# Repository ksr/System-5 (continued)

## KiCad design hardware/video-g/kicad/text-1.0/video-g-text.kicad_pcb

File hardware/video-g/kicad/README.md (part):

# VIDEO-G 1.0 - KiCad

The two boards of VIDEO-G (design: [`../DESIGN.md`](../DESIGN.md)). **Generated, not hand-edited:** each board's
circuit is `gen/netlist.py`, its placement `gen/place.py`; `common/build.sh` makes everything else from them. Not
ordered; not built.

| Folder | Board | Size | ICs | Parts list |
|---|---|---|---|---|
| `text-1.0/` | VIDEO-G 1.0 TEXT: 6845 + IDT7134 text, status register, PS/2 keyboard, RCA + DE-9, every decode (all memory-mapped, 7000-7FFF) | **188 x 106.6 mm** (47 mm longer than a standard card: Ken keeps it, 2026-11-17; and since 2026-11-18 10.4 mm more at the +5V end, for the 36-pin bus connector) | 24 | [`text-1.0/BOM.md`](text-1.0/BOM.md) |
| `gfx-1.0/` | VIDEO-G 1.0 GFX: 62256 graphics (two pages), Y and control registers, PS/2 mouse, PWR LED | 141 x 96 mm (standard) | 19 | [`gfx-1.0/BOM.md`](gfx-1.0/BOM.md) |

Both: 4 layers (F.Cu / B.Cu signals, In1.Cu a solid GND plane, In2.Cu a solid +5V plane: MEM3-E's stack-up), the
System-5 bus connector (GFX the 30-pin one; TEXT the 36-pin one since 2026-11-18, for its keyboard flag's choice of four
EF lines: its positions 1-30 where the 30-pin connector's pins were, the board grown at the +5V end) and card-guide
keep-outs where every card has them, the 2 x 20 ribbon header along the same
side edge 78-138 mm from the bus edge (pins 83.6-131.9 mm) (TEXT J6, GFX J4: a straight 40-way cable between neighbouring slots; pin map
`common/ribbon.py`). Silkscreen per Ken's rules: every reference outside its part with the IC type beside it, jacks,
jumpers and the LED labelled by function, the board name and cottageworker.com. **Since 2026-11-18 every text reads
upright with the card standing in the bus, connector down** (Ken's rule for every board; he asked for it on TEXT and
GFX that day): KiCad angle 270, each label at the first spot clear of every pad, part, other text and the card-guide
strips, under its part with the card standing first (`common/silk.py` with `tools/kicad/silk270.py`); the bus pins'
names in two staggered columns (the backplane's names on both boards: `+5V`, `-RESET`); the jumpers' settings at their
ends (TEXT's JP1 NTSC / 5151, JP2 + / -); the name line alone at angle 0 along the bottom edge as drawn, just above the
guide strip (up the right-hand side standing). The copper did not change: `common/silk.py <board>` rewrote the
silkscreen of the routed boards, every track, via, pad and zone checked the same.

**The bus connector is drawn as the part it is since the night of 2026-11-18.** J1 is a single-row right-angle pin
header: its plastic body lies on the board between the pads and the card edge, 1.5 to 4.0 mm from the pads, and its
pins run on past the edge (the photos of the built MEM3-E and BUSDRV-B show it). The C30 and C36 footprints had pads
and a courtyard round them and nothing else, so the label placer and `pcb-check` both took that strip for free board:
`J1 BUS` was printed there on both boards, part of it under the header, and half of TEXT's JP1 label with it. Both
footprints now carry the body (F.Fab), a courtyard round body and pads, and KiCad's 3D model of the header, so the
renders show the connector and the placer keeps every label off it. `J1 BUS` stands past the header's +5V end on GFX
and beside the pin names, between IC1 and IC2, on TEXT; TEXT's `JP1 MONITOR` is under its jumper in the corner past
the header's GND end, `NTSC` and `5151` at the jumper's ends. Silkscreen only, again: `common/silk.py <board>` brings
J1's drawing up to its library file (`tools/kicad/fp_update.py`) and places the labels afresh, and it and
`common/make_board.py` now stop with an error when a label finds no room (the label had been left out without a word).

## Files (per board)

| File | What |
|---|---|
| `gen/netlist.py` | THE circuit: parts, nets, no-connects, what to buy; `python3 gen/netlist.py` checks every symbol pin |
| `gen/place.py` | the placement, silkscreen labels and texts |
| `<board>.kicad_sch` | the working schematic (one sheet, net labels): ERC, the board's parity |
| `<board>.kicad_pcb` | the routed board |
| `schematic/` | the readable schematic, redrawn and proven by `tools/kicad/sch/gen_schematic.py` (in the book `docs/manual/pdf/system5-schematics.pdf`) |
| `reports/` | ERC, DRC, the exported netlist |
| `<board>-gerbers.zip`, `gerbers/`, `check-*.png` | the order files and one picture per copper layer from them |
| `BOM.md` | the parts list (`common/bom.py`) |
| `pcb-check.ini` | `pcb-check`'s settings: name, rev, size, slot pitch, the bus edge, the bus pin list (`tools/s5bus.py`, the bus Rev D's pin names), the system's tests |

`common/`: `symlib.py` (symbol pins from the KiCad libraries), `ribbon.py`, `make_schematic.py`, `checknet.py` (the
exported netlist = `netlist.py`), `make_board.py`, `route.py` (Freerouting in and out, the inner layers as planes),
`route_leftovers.py` (the few connections Freerouting leaves; copied from MEM3-E's), `silk.py` (every label, also on
a routed board: `<KiCad python> common/silk.py <board>` changes the silkscreen only), `bom.py`, `build.sh`.
`lib/video-g-local`: IDT7134, Mini-DIN, RCA and DE-9 from YACC1's Video V2.0 (copied), System-5's C30 bus connector
(GFX), the 36-pin C36 (TEXT; the other 36-pin cards' footprint) and 0.1" bypass-cap footprints (the C30 labels'
stroke raised to 0.15 mm for the fab; 2026-11-17: a courtyard on both and an F.Fab body, 4.0 x 2.5 mm, on the cap, so
that `pcb-check` knows where they are and finds each cap's "100n"; 2026-11-18: the right-angle header's body, a
courtyard round it and its 3D model on C30 and C36, above; 2026-11-19: the RCA jack's body on F.Fab, the outline its
silkscreen has, for `pcb-check`'s new BODIES line, which names a part with nothing drawn on the fab layer: TEXT's J2
was the one. `J2 RCA COMPOSITE` moved 0.15 mm with it, the label placer going by the body where it had gone by the
courtyard). The DE-9, Eagle's F09HP, had only its nine pins' tails on the fab layer, 11 x 3.6 mm of a 31 x 14 mm
connector, which `pcb-check` took for the whole part (its BODIES line names such a drawing since its `0e99e19`): the
connector's outer line is on F.Fab now, and `J3 DE-9 TTL 5151` keeps its place by a spot of its own in `place.py`, the
1.5 mm between the DE-9's back and R4's lead being narrower than the placer's steps. `common/silk.py <board>` brings
the drawing of every part from this library up to its file before it places the labels.

## Rebuild

```sh
hardware/video-g/kicad/common/build.sh hardware/video-g/kicad/gfx-1.0
hardware/video-g/kicad/common/build.sh hardware/video-g/kicad/text-1.0
```

KiCad 10 and Freerouting 1.9 (`~/freerouting/freerouting.jar`). It runs: the netlist check, the schematic and ERC,
the netlist proof, the unrouted board, Freerouting (`MP` passes at most, default 100), the leftover router, DRC with the zones
refilled and schematic parity, the order files, and `tools/preorder_check.py --layers 4`.

**The routing is reproducible since 2026-11-17.** `route.py` writes Freerouting's input in a fixed order and without
the parts' drawn outlines: KiCad lists components, images and pins in a different order on every build (new UUIDs),
and Freerouting's result follows that order and even the outlines (adding two courtyards turned a complete route into
one that stalled), so one build of TEXT left VMA open where the build before had routed everything. Now the same
`gen/` files give the same board. `ROUTE_SEED` in `gen/place.py` shuffles the order reproducibly when one leaves a
net open: TEXT used 7 to 2026-11-24 (seeds 0-10 tried in 2026-11-17's form: nine routed every net, 7 soonest), 0 since. GFX uses 0, the sorted order: rebuilt
the evening of 2026-11-17 with its power LED, it routed every net at once (1697 track segments, 97 vias). The ordering
code is `tools/kicad/dsn_order.py` since then, shared with CPU Rev D (`route.py` gives the same input as before).

**TEXT was routed again on 2026-11-18**, for the 36-pin connector and the 2 x 4 KBD FLAG block: seed 7 still routes
every net (2616 track segments, 133 vias; 3 minutes of routing, then 72 minutes of Freerouting's optimization, so a
full build of TEXT takes about an hour and a quarter). The silkscreen work after it did not need another: a new build
gives Freerouting the same input, byte for byte but for the file's own path, and the same silkscreen to the micrometre
(checked in a copy of the tree).

**TEXT was routed again on 2026-11-24**, with its 6845 write-only (`DESIGN.md`, section 4: seven pins moved, no part and no
silkscreen text changed): seed 0, 2483 track segments and 152 vias. Freerouting routed every net in 4 minutes and then
shortened the tracks for 70; the leftover router had nothing to do; DRC 0 errors and 0 warnings. (Seed 7 routed every net too, but
the track the leftover router made beside J1's pins broke the 0.20 mm clearance in six places.) The 83 parts stand where they
stood, and of the 133 silkscreen texts one moved: `C22 100n`, 0.5 mm, at its size (`place.SPOTS`, `SIZES`; Ken: "move the C22
label clear of IC22"). A 14-pin chip is 19.3 mm long, 0.65 mm past each end of the socket the placer goes by, and the label's
end had been 0.15 mm under it; it is 0.35 mm clear now. Silkscreen only: copper, masks, outline and drills as routed.

After a build: `python3 common/bom.py <board>` and, for the book, `python3 tools/kicad/sch/gen_schematic.py <board>/schematic` and
`python3 tools/kicad/sch/make_book.py`.

## Before ordering

**The latest result, of both boards as they are now (TEXT routed again with its 6845 write-only, 2026-11-24): QA's
run of 2026-11-25 at elf `38fc4d0`, `pcb-check --tests`: TEXT no failures, 0 warnings (netlist 160 of 160; the copper
rebuilt from the gerbers by two methods, which agree; 16 of 16 faults planted in copies of the zip noticed); GFX no
failures, 0 warnings (124 of 124; 16 of 16). The same NOTE on TEXT's EFOC as below. `tools/qa.py full` at `38fc4d0`:
OK.** The results below are of TEXT before that route.

**`pcb-check`, the check before an order (Ken, every system, since 2026-11-06; `hardware/BUILD-RULES.md`, section 2):
both boards as they were before TEXT's route of 2026-11-24, with `--tests`, 2026-11-19: GFX at elf `77257f1` (run by the pcb-check session); TEXT at
`77257f1` (the same), at `688e6ed` after its four KBD FLAG names moved 0.5 mm off JP3's outline, at `b4692e9`
(pcb-check `bd032dd`, with its new BODIES line) after the RCA jack's body went on the fab layer, and at `b2252b7`
(pcb-check `0b45f65`) after the DE-9's; GFX again at `b2252b7` without its tests, the board unchanged:**

```sh
~/Developer/pcb-check/pcb-check hardware/video-g/kicad/text-1.0/video-g-text.kicad_pcb hardware/video-g/kicad/text-1.0/video-g-text-gerbers.zip --layers 4 --tests
~/Developer/pcb-check/pcb-check hardware/video-g/kicad/gfx-1.0/video-g-gfx.kicad_pcb hardware/video-g/kicad/gfx-1.0/video-g-gfx-gerbers.zip --layers 4 --tests
```

| Board | Result | For Ken's eye |
|---|---|---|
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
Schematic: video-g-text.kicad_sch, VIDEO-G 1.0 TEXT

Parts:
C1, C2, C3, C4, C5, C6, C7, C8, C9, C10, C11, C12, C13, C14, C15, C16, C17, C18, C19, C20, C21, C22, C23, C24, C25, C27: 100n; C025-050X050
C26: 47u 16V; CP_Radial_D6.3mm_P2.50mm
C28, C29: 22p; C025-050X050
F1: 0.5A PTC; Fuse_Bourns_MF-RHT050
IC1: 74HCT373; DIP-20_W7.62mm_Socket
IC2: 74LS85; DIP-16_W7.62mm_Socket
IC3: IDT7134; DIP-48_W15.24mm_Socket
IC4: HD68B45SP; DIP-40_W15.24mm_Socket
IC5, IC6, IC7: 74HCT138; DIP-16_W7.62mm_Socket
IC8: 74LS244; DIP-20_W7.62mm_Socket
IC9: 74HCT374; DIP-20_W7.62mm_Socket
IC10: ATmega328P-PU; DIP-28_W7.62mm_Socket
IC11: 74LS374; DIP-20_W7.62mm_Socket
IC12: AT28C64B-15; DIP-28_W15.24mm_Socket
IC13: 74LS166; DIP-16_W7.62mm_Socket
IC14: 74LS175; DIP-16_W7.62mm_Socket
IC15: 74F163A; DIP-16_W7.62mm_Socket
IC16, IC17: 74LS04; DIP-14_W7.62mm_Socket
IC18: 74HCT08; DIP-14_W7.62mm_Socket
IC19: 74LS08; DIP-14_W7.62mm_Socket
IC20: 74LS32; DIP-14_W7.62mm_Socket
IC21: 74LS10; DIP-14_W7.62mm_Socket
IC22: 74LS86; DIP-14_W7.62mm_Socket
IC23: 7416; DIP-14_W7.62mm_Socket
IC24: 74HCT74; DIP-14_W7.62mm_Socket
J1: System-5 bus (36); C36
J2: RCA
J3: DE-9 F; F09HP
J4: KEYBOARD; MiniDIN6_MD-60SM
J5: FTDI; PinHeader_1x06_P2.54mm_Vertical
J6: TO GFX; IDC-Header_2x20_P2.54mm_Vertical
JP1: MONITOR; PinHeader_1x03_P2.54mm_Vertical
JP2: VSYNC; PinHeader_1x03_P2.54mm_Vertical
JP3: KBD FLAG; PinHeader_2x04_P2.54mm_Vertical
LED1: PWR; LED_D5.0mm
R1, R2, R3: 1k; R_Axial_DIN0207_L6.3mm_D2.5mm_P2.54mm_Vertical
R4, R11, R12, R13: 33; R_Axial_DIN0207_L6.3mm_D2.5mm_P2.54mm_Vertical
R5: 270; R_Axial_DIN0207_L6.3mm_D2.5mm_P2.54mm_Vertical
R6: 330; R_Axial_DIN0207_L6.3mm_D2.5mm_P2.54mm_Vertical
R7: 10k; R_Axial_DIN0207_L6.3mm_D2.5mm_P2.54mm_Vertical
R8, R9, R10: 4.7k; R_Axial_DIN0207_L6.3mm_D2.5mm_P2.54mm_Vertical
RN1: 10k x4; R_Array_SIP5
RN2, RN3: 10k x5; R_Array_SIP6
SV1: BLOCK; PinHeader_2x04_P2.54mm_Vertical
Y1: 12MHz; Crystal_HC49-U_Vertical
Y2: 16MHz; Crystal_HC49-U_Vertical

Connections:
+5V: C1.1, C2.1, C3.1, C4.1, C5.1, C6.1, C7.1, C8.1, C9.1, C10.1, C11.1, C12.1, C13.1, C14.1, C15.1, C16.1, C17.1, C18.1, C19.1, C20.1, C21.1, C22.1, C23.1, C24.1, C25.1, C26.1, F1.1, IC1.20 (VCC), IC2.16 (VCC), IC3.2 (R/~WL), IC3.48 (VCC), IC4.20 (VCC), IC5.16 (VCC), IC6.16 (VCC), IC7.16 (VCC), IC8.17 (I3b), IC8.20 (VCC), IC9.20 (VCC), IC10.7 (VCC), IC10.20 (AVCC), IC11.20 (VCC), IC12.27 (~WE), IC12.28 (VCC), IC13.16 (VCC), IC14.16 (VCC), IC15.1 (~MR), IC15.6 (D3), IC15.16 (VCC), IC16.14 (VCC), IC17.14 (VCC), IC18.5, IC18.14 (VCC), IC19.14 (VCC), IC20.14 (VCC), IC21.9, IC21.11, IC21.14 (VCC), IC22.14 (VCC), IC23.14 (VCC), IC24.1 (~R), IC24.4 (~S), IC24.10 (~S), IC24.12 (D), IC24.14 (VCC), J1.30, JP1.3, R3.2, R5.1, R6.2, R7.2, R8.2, R9.2, R10.2, RN1.1 (common), RN2.1 (common)
/-BOARDSEL: IC17.6, IC20.12
/-CRTCCS: IC4.25 (~CS), IC5.15 (O0)
/-EF: J1.6, JP3.7, RN2.2 (R1)
/-EF1: J1.31, JP3.1
/-EF2: J1.32, JP3.3
/-EF3: J1.33, JP3.5
/-MRD: IC3.43 (~OER), IC6.5 (E2), J1.18
/-MRW: IC3.46 (R/~WR), IC7.5 (E2), J1.17
/-RDKEY: IC6.14 (O1), IC9.1 (OE), IC20.9
/-RDMOUSE: IC6.12 (O3), J6.31
/-RDSTAT: IC6.13 (O2), IC8.1 (OEa), IC8.19 (OEb)
/-RESET: IC4.2 (~RESET), IC18.4, IC19.5, J1.4, RN2.4 (R3)
/-TXTCE: IC3.47 (~CER), IC20.11
/-VMA: IC16.9, J1.5, RN2.3 (R2)
/-WRCRTC: IC7.15 (O0), IC21.10
/-WRCTL: IC7.13 (O2), J6.26
/-WRY: IC7.12 (O3), J6.30
/A0: IC1.3 (D0), IC3.42 (A0R), IC4.24 (RS), J1.16
/A1: IC1.4 (D1), IC3.41 (A1R), IC5.1 (A0), IC6.1 (A0), IC7.1 (A0), J1.15
/A2: IC1.7 (D2), IC3.40 (A2R), IC5.2 (A1), IC6.2 (A1), IC7.2 (A1), J1.14
/A3: IC1.8 (D3), IC3.39 (A3R), J1.13
/A4: IC1.13 (D4), IC3.38 (A4R), J1.12
/A5: IC1.14 (D5), IC3.37 (A5R), J1.11
/A6: IC1.17 (D6), IC3.36 (A6R), J1.10
/A7: IC1.18 (D7), IC3.35 (A7R), J1.9
/A8: IC1.2 (O0), IC3.34 (A8R)
/A9: IC1.5 (O1), IC3.33 (A9R)
/A10: IC1.6 (O2), IC3.44 (A10R), IC5.4 (E1), IC6.4 (E1), IC7.4 (E1), IC19.13
/A11: IC1.9 (O3), IC18.13, IC20.13
/A12: IC1.12 (O4), IC2.9 (B0)
/A13: IC1.15 (O5), IC2.11 (B1)
/A14: IC1.16 (O6), IC2.14 (B2)
/A15: IC1.19 (O7), IC2.1 (B3)
/ATTR1: IC14.4 (D0), IC22.3
/ATTR2: IC14.2 (Q0), IC14.5 (D1)
/ATTR3: IC14.7 (Q1), IC22.4
/BOARDSEL: IC2.6 (Oa=b), IC17.5, IC18.12
/CA3: IC11.2 (O0), IC12.7 (A3)
/CA4: IC11.5 (O1), IC12.6 (A4)
/CA5: IC11.6 (O2), IC12.5 (A5)
/CA6: IC11.9 (O3), IC12.4 (A6)
/CA7: IC11.12 (O4), IC12.3 (A7)
/CA8: IC11.15 (O5), IC12.25 (A8)
/CA9: IC11.16 (O6), IC12.24 (A9)
/CG0: IC12.11 (I/O0), IC13.2 (A)
/CG1: IC12.12 (I/O1), IC13.3 (B)
/CG2: IC12.13 (I/O2), IC13.4 (C)
/CG3: IC12.15 (I/O3), IC13.5 (D)
/CG4: IC12.16 (I/O4), IC13.10 (E)
/CG5: IC12.17 (I/O5), IC13.11 (F)
/CG6: IC12.18 (I/O6), IC13.12 (G)
/CG7: IC12.19 (I/O7), IC13.14 (H)
/CHARCLOCK: IC11.11 (Cp), IC13.15 (PE), IC14.9 (Cp), IC15.9 (~PE), IC16.12, R12.1
/CNTEN: IC13.9 (Clr), IC14.1 (~Mr), IC15.7 (CEP), IC15.10 (CET), R3.1
/CNTQA: IC15.14 (Q0), IC22.12
/CNTQB: IC15.13 (Q1), IC22.13
/CRTCCLK: IC4.21 (CLK), IC15.12 (Q2), IC20.4, R13.1
/CRTCE: IC4.23 (E), IC21.8
/CURSOR: IC4.19 (CURSOR), IC22.1
/D0: IC3.25 (I/O0R), IC4.33 (D0), IC8.18 (O0a), IC9.2 (O0), J1.29
/D1: IC3.26 (I/O1R), IC4.32 (D1), IC8.16 (O1a), IC9.5 (O1), J1.28
/D2: IC3.27 (I/O2R), IC4.31 (D2), IC8.14 (O2a), IC9.6 (O2), J1.27
/D3: IC3.28 (I/O3R), IC4.30 (D3), IC8.12 (O3a), IC9.9 (O3), J1.26
/D4: IC3.29 (I/O4R), IC4.29 (D4), IC8.9 (O0b), IC9.12 (O4), J1.25
/D5: IC3.30 (I/O5R), IC4.28 (D5), IC8.7 (O1b), IC9.15 (O5), J1.24
/D6: IC3.31 (I/O6R), IC4.27 (D6), IC8.5 (O2b), IC9.16 (O6), J1.23
/D7: IC3.32 (I/O7R), IC4.26 (D7), IC8.3 (O3b), IC9.19 (O7), J1.22
/DE: IC4.18 (DE), IC8.8 (I3a), IC14.12 (D2)
/DE2: IC14.10 (Q2), IC14.13 (D3)
/DE3: IC14.15 (Q3), IC21.5
/DE9VS: J3.9, JP2.2
/DOTCLK: IC13.7 (Clk), IC15.2 (CP), IC16.6, R11.1
/EFOC: IC23.8, JP3.2, JP3.4, JP3.6, JP3.8
/FDTR: C27.1, J5.6
/FRX: IC10.3 (PD1), J5.5
/FTX: IC10.2 (PD0), J5.4
/GDOT: IC20.2, IC21.2, J6.33, RN3.3 (R2)
/GFXPRES: IC8.13 (I1b), J6.36, RN3.5 (R4)
/GOR: IC20.3, IC21.3
/HSBUF: IC19.8, IC23.5, J3.8
/HSYNC: IC4.39 (HS), IC19.9, IC19.10
/KCLK: IC10.4 (PD2), J4.5 (CLK), R9.1
/KCLR: IC19.6, IC24.13 (~R)
/KDAT: IC10.6 (PD4), J4.1 (DATA), R10.1
/KRDT: IC19.4, IC20.8
/KREADY: IC8.2 (I0a), IC10.16 (PB2), IC23.9, IC24.9 (Q)
/LDDATA: IC9.11 (Cp), IC10.12 (PD6), IC24.11 (C), RN2.5 (R4)
/MA0: IC3.6 (A0L), IC4.4 (MA0), J6.2
/MA1: IC3.7 (A1L), IC4.5 (MA1), J6.3
/MA2: IC3.8 (A2L), IC4.6 (MA2), J6.4
/MA3: IC3.9 (A3L), IC4.7 (MA3), J6.5
/MA4: IC3.10 (A4L), IC4.8 (MA4), J6.6
/MA5: IC3.11 (A5L), IC4.9 (MA5), J6.7
/MA6: IC3.12 (A6L), IC4.10 (MA6), J6.8
/MA7: IC3.13 (A7L), IC4.11 (MA7), J6.9
/MA8: IC3.14 (A8L), IC4.12 (MA8), J6.10
/MA9: IC3.15 (A9L), IC4.13 (MA9), J6.11
/MA10: IC3.4 (A10L), IC4.14 (MA10), J6.12
/MA11: IC3.3 (A11L), IC4.15 (MA11)
/MD0: IC9.3 (D0), IC10.23 (PC0)
/MD1: IC9.4 (D1), IC10.24 (PC1)
/MD2: IC9.7 (D2), IC10.25 (PC2)
/MD3: IC9.8 (D3), IC10.26 (PC3)
/MD4: IC9.13 (D4), IC10.27 (PC4)
/MD5: IC9.14 (D5), IC10.28 (PC5)
/MD6: IC9.17 (D6), IC10.14 (PB0)
/MD7: IC9.18 (D7), IC10.15 (PB1)
/MONITOR: IC8.11 (I0b), JP1.2, RN3.2 (R1)
/MREADY: IC8.4 (I1a), J6.35, RN3.4 (R3)
/MRST: C27.2, IC10.1 (~RESET/PC6), IC23.12, R7.1
/NBOTH: IC21.4, IC21.12
/NVSYNC: IC17.8, JP2.3
/OSCIN: IC16.1, R1.1, Y1.1
/OSCMID: IC16.2, IC16.3, R1.2, R2.1
/OSCOUT: IC16.4, IC16.5, R2.2, Y1.2
/PS2VCC: F1.2, J4.4 (+5V)
/PWRLED: LED1.2 (A), R6.1
/QCR: IC20.6, J6.23
/RA0: IC4.38 (RA0), IC12.10 (A0), J6.13
/RA1: IC4.37 (RA1), IC12.9 (A1), J6.14
/RA2: IC4.36 (RA2), IC12.8 (A2), J6.15
/RCHARCLK: J6.19, R12.2
/RCO: IC15.15 (TC), IC16.13, IC20.5
/RDOTCLK: J6.17, R11.2
/RESETB: IC18.6, IC23.11
/RESETH: IC23.10, IC23.13, R8.1
/RQC: J6.21, R13.2
/SEL0: IC2.10 (A0), RN1.2 (R1), SV1.7
/SEL1: IC2.12 (A1), RN1.3 (R2), SV1.5
/SEL2: IC2.13 (A2), RN1.4 (R3), SV1.3
/SEL3: IC2.15 (A3), RN1.5 (R4), SV1.1
/SYNC: IC23.4, IC23.6, J2.C1 (C), R4.1, R5.2
/TD: IC19.1, IC22.6
/TDG: IC19.3, IC20.1, IC21.1
/TDOT: IC13.13 (Qh), IC22.5
/TEXTON: IC19.2, J6.27, RN2.6 (R5)
/TPA: IC1.11 (LE), J1.20
/TPB: IC17.3, J1.19
/TPBN: IC17.4, IC20.10
/UPPER: IC5.6 (E3), IC6.6 (E3), IC7.6 (E3), IC18.11, IC19.12
/VD0: IC3.16 (I/O0L), IC11.3 (D0)
/VD1: IC3.17 (I/O1L), IC11.4 (D1)
/VD2: IC3.18 (I/O2L), IC11.7 (D2)
/VD3: IC3.19 (I/O3L), IC11.8 (D3)
/VD4: IC3.20 (I/O4L), IC11.13 (D4)
/VD5: IC3.21 (I/O5L), IC11.14 (D5)
/VD6: IC3.22 (I/O6L), IC11.17 (D6)
/VD7: IC3.23 (I/O7L), IC22.2
/VIDEO: IC23.2, J3.7, R4.2
/VIDN: IC21.6, IC23.1
/VMA: IC2.3 (Ia=b), IC16.8
/VSBUF: IC17.9, IC18.3, IC23.3, JP2.1
/VSYNC: IC4.40 (VS), IC8.6 (I2a), IC18.1, IC18.2
/WEPH: IC22.11, J6.24
/WSEL: IC19.11, J6.29
/XORM: IC21.13, J6.28, RN3.6 (R5)
/XT1: C28.1, IC10.9 (XTAL1/PB6), Y2.1
/XT2: C29.1, IC10.10 (XTAL2/PB7), Y2.2
GND: C1.2, C2.2, C3.2, C4.2, C5.2, C6.2, C7.2, C8.2, C9.2, C10.2, C11.2, C12.2, C13.2, C14.2, C15.2, C16.2, C17.2, C18.2, C19.2, C20.2, C21.2, C22.2, C23.2, C24.2, C25.2, C26.2, C28.2, C29.2, IC1.1 (OE), IC1.10 (GND), IC2.2 (Ia<b), IC2.4 (Ia>b), IC2.8 (GND), IC3.1 (~CEL), IC3.5 (~OEL), IC3.24 (GND), IC3.45 (A11R), IC4.1 (GND), IC4.3 (LPSTB), IC4.22 (R/~W), IC5.3 (A2), IC5.5 (E2), IC5.8 (GND), IC6.3 (A2), IC6.8 (GND), IC7.3 (A2), IC7.8 (GND), IC8.10 (GND), IC8.15 (I2b), IC9.10 (GND), IC10.8 (GND), IC10.22 (GND), IC11.1 (OE), IC11.10 (GND), IC11.18 (D7), IC12.2 (A12), IC12.14 (GND), IC12.20 (~CE), IC12.21 (A10), IC12.22 (~OE), IC12.23 (A11), IC13.1 (Ds), IC13.6 (CE), IC13.8 (GND), IC14.8 (GND), IC15.3 (D0), IC15.4 (D1), IC15.5 (D2), IC15.8 (GND), IC16.7 (GND), IC16.11, IC17.1, IC17.7 (GND), IC17.11, IC17.13, IC18.7 (GND), IC18.9, IC18.10, IC19.7 (GND), IC20.7 (GND), IC21.7 (GND), IC22.7 (GND), IC22.9, IC22.10, IC23.7 (GND), IC24.2 (D), IC24.3 (C), IC24.7 (GND), J1.1, J2.S1 (S), J2.S2 (S), J2.S3 (S), J3.1, J3.2, J3.G1 (SHELL), J3.G2 (SHELL), J4.3 (GND), J4.S (SHELL), J5.1, J5.2, J6.1, J6.16, J6.18, J6.20, J6.22, J6.25, J6.32, J6.34, J6.37, J6.38, J6.39, J6.40, JP1.1, LED1.1 (K), RN3.1 (common), SV1.2, SV1.4, SV1.6, SV1.8

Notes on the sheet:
VIDEO-G 1.0 TEXT (hardware/video-g/DESIGN.md): the System-5 text card of VIDEO-G; works alone, or with the GFX board on the J6 ribbon.
Memory-mapped, no I/O ports (2026-11-17). Block jumper SV1: 1-2 only = block 7. 7000-77FF text RAM (IDT7134); 7C00-7FFF the GFX window (WSEL).
Registers (7800-7BFF, pairs repeating): 7800/7801 the 6845 (RS = A0); 7802 key (+ a bus flag line while KEY-READY: JP3 picks -EF1, -EF2, -EF3 or -EF); 7804 status / control (GFX); 7806 mouse / Y (GFX).
Status: 0 KEY-READY 1 MOUSE-READY 2 VSYNC 3 DE 4 MONITOR 5 GFX-PRESENT, 7-6 = 10. Reads while -MRD is low; writes while -MRW is low.
6845: write-only (2026-11-24): R/-W on ground, E = the whole -MRW time of a write to 7800/7801 (IC7, IC21C); a read of 7800/7801 finds nothing.

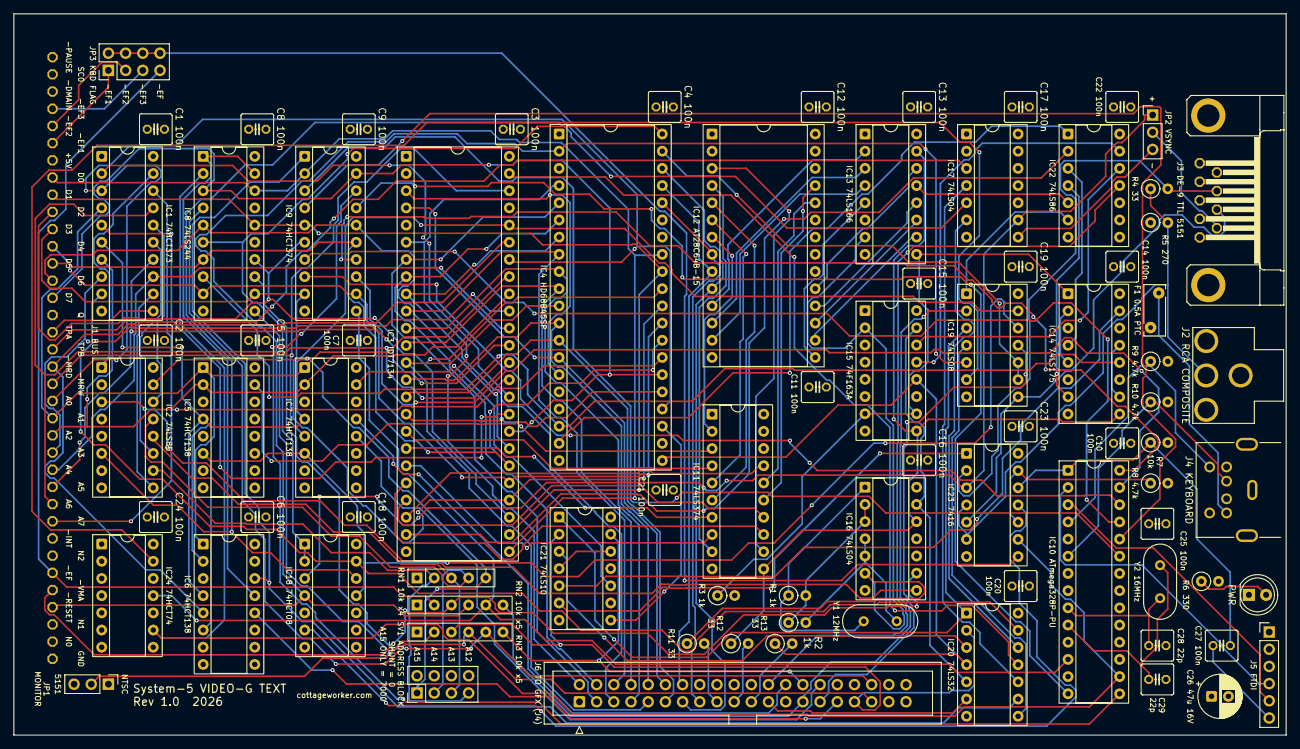
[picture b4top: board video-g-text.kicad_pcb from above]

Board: 4 copper layers, 188.0 x 106.6 mm, 83 parts (0 on the bottom side), 160 nets.

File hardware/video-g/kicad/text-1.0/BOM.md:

# VIDEO-G 1.0 TEXT - bill of materials

Written by `hardware/video-g/kicad/common/bom.py` from `gen/netlist.py` (2026-11-24). Every IC goes in a socket.

| Qty | Value | Footprint | References | What to buy |
|---|---|---|---|---|
| 1 | 74HCT373 | DIP-20_W7.62mm_Socket | IC1 | 74HCT373 (CMOS inputs: no load on the 1802's address lines) |
| 1 | 74LS85 | DIP-16_W7.62mm_Socket | IC2 |  |
| 1 | IDT7134 | DIP-48_W15.24mm_Socket | IC3 | IDT7134SA or LA, 55-90 ns, DIP-48 (600 mil); the 6845 card's chip also fits |
| 1 | HD68B45SP | DIP-40_W15.24mm_Socket | IC4 | HD68B45SP (Hitachi) or MC68B45P (Motorola), the 2 MHz grade; since the 6845 is write-only (E = the whole -MRW) the bus timing of a 1 MHz part, such as the 6845 card's HD6845, is enough as well (DESIGN.md section 4) |
| 3 | 74HCT138 | DIP-16_W7.62mm_Socket | IC5, IC6, IC7 | 74HCT138 (CMOS inputs on the bus address) |
| 1 | 74LS244 | DIP-20_W7.62mm_Socket | IC8 |  |
| 1 | 74HCT374 | DIP-20_W7.62mm_Socket | IC9 |  |
| 1 | ATmega328P-PU | DIP-28_W7.62mm_Socket | IC10 | ATmega328P-PU with the Arduino Uno bootloader burned (ISP) before fitting |
| 1 | 74LS374 | DIP-20_W7.62mm_Socket | IC11 |  |
| 1 | AT28C64B-15 | DIP-28_W15.24mm_Socket | IC12 | AT28C64B-15PU (Microchip), burned on the T48 with firmware/video-g-chargen/video-g-chargen.bin |
| 1 | 74LS166 | DIP-16_W7.62mm_Socket | IC13 |  |
| 1 | 74LS175 | DIP-16_W7.62mm_Socket | IC14 |  |
| 1 | 74F163A | DIP-16_W7.62mm_Socket | IC15 | 74F163A or 74ALS163B (V2.0 review R3-1: CHARCLOCK set-up to the 166's SH/-LD); keep a spare |
| 2 | 74LS04 | DIP-14_W7.62mm_Socket | IC16, IC17 |  |
| 1 | 74HCT08 | DIP-14_W7.62mm_Socket | IC18 |  |
| 1 | 74LS08 | DIP-14_W7.62mm_Socket | IC19 |  |
| 1 | 74LS32 | DIP-14_W7.62mm_Socket | IC20 |  |
| 1 | 74LS10 | DIP-14_W7.62mm_Socket | IC21 |  |
| 1 | 74LS86 | DIP-14_W7.62mm_Socket | IC22 |  |
| 1 | 7416 | DIP-14_W7.62mm_Socket | IC23 |  |
| 1 | 74HCT74 | DIP-14_W7.62mm_Socket | IC24 |  |
| 1 | 12MHz | Crystal_HC49-U_Vertical | Y1 | 12 MHz, HC-49/U |
| 1 | 16MHz | Crystal_HC49-U_Vertical | Y2 | 16 MHz, HC-49/U, 18-20 pF load |
| 1 | System-5 bus (36) | C36 | J1 | 1 x 36 right-angle pin header, 2.54 mm, single row (cut from a 1 x 40): its plastic body lies between the pads and the card edge, the pins out past the edge |
| 1 | RCA | RCA | J2 | RCA jack, right-angle PCB mount (YACC1 V1.0 card's footprint) |
| 1 | DE-9 F | F09HP | J3 | DE-9 female, right-angle PCB mount (F09HP footprint: 2.74 mm pitch, 2.54 mm between rows) |
| 1 | KEYBOARD | MiniDIN6_MD-60SM | J4 | Same Sky (CUI Devices) MD-60SM, date code after 2022-03-03 |
| 1 | FTDI | PinHeader_1x06_P2.54mm_Vertical | J5 | 1 x 6 pin header, 2.54 mm (an FTDI cable programs the ATmega) |
| 1 | TO GFX | IDC-Header_2x20_P2.54mm_Vertical | J6 | 2 x 20 shrouded box header, 2.54 mm; 40-way IDC ribbon (two 2 x 20 IDC sockets, about 10 cm) |
| 1 | BLOCK | PinHeader_2x04_P2.54mm_Vertical | SV1 | 2 x 4 pin header + 1 shunt on 1-2 (block 7, 7000); each fitted shunt is a 0 bit |
| 1 | MONITOR | PinHeader_1x03_P2.54mm_Vertical | JP1 | 1 x 3 pin header + shunt: 1-2 NTSC, 2-3 IBM 5151 |
| 1 | VSYNC | PinHeader_1x03_P2.54mm_Vertical | JP2 | 1 x 3 pin header + shunt: 1-2 +VSYNC, 2-3 -VSYNC (5151) |
| 1 | KBD FLAG | PinHeader_2x04_P2.54mm_Vertical | JP3 | 2 x 4 pin header + 1 shunt: the keyboard flag on -EF1, -EF2, -EF3 or -EF (set to -EF, the fourth pair) |
| 1 | 0.5A PTC | Fuse_Bourns_MF-RHT050 | F1 | Bourns MF-RHT050 (0.5 A hold, radial) |
| 1 | PWR | LED_D5.0mm | LED1 |  |
| 1 | 10k x4 | R_Array_SIP5 | RN1 | 10k x4 BUSSED, pin 1 common, 5-pin SIP (e.g. Bourns 4605X-101-103LF) |
| 2 | 10k x5 | R_Array_SIP6 | RN2, RN3 | 10k x5 BUSSED, pin 1 common, 6-pin SIP (e.g. Bourns 4606X-101-103LF) |
| 3 | 1k | R_Axial_DIN0207_L6.3mm_D2.5mm_P2.54mm_Vertical | R1, R2, R3 | 1/4 W metal film, mounted standing |
| 4 | 33 | R_Axial_DIN0207_L6.3mm_D2.5mm_P2.54mm_Vertical | R4, R11, R12, R13 | 1/4 W metal film, mounted standing |
| 1 | 270 | R_Axial_DIN0207_L6.3mm_D2.5mm_P2.54mm_Vertical | R5 | 1/4 W metal film, mounted standing |
| 1 | 330 | R_Axial_DIN0207_L6.3mm_D2.5mm_P2.54mm_Vertical | R6 | 1/4 W metal film, mounted standing |
| 1 | 10k | R_Axial_DIN0207_L6.3mm_D2.5mm_P2.54mm_Vertical | R7 | 1/4 W metal film, mounted standing |
| 3 | 4.7k | R_Axial_DIN0207_L6.3mm_D2.5mm_P2.54mm_Vertical | R8, R9, R10 | 1/4 W metal film, mounted standing |
| 26 | 100n | C025-050X050 | C1, C2, C3, C4, C5, C6, C7, C8, C9, C10, C11, C12, C13, C14, C15, C16, C17, C18, C19, C20, C21, C22, C23, C24, C25, C27 | ceramic X7R, 50 V, 0.1 in (2.54 mm) lead spacing |
| 1 | 47u 16V | CP_Radial_D6.3mm_P2.50mm | C26 | 47 uF electrolytic, 16 V or more, radial 6.3 mm, 2.5 mm pitch |
| 2 | 22p | C025-050X050 | C28, C29 | ceramic C0G (NP0), 50 V, 0.1 in lead spacing |

**IC sockets:** 9 x DIP-14, 300 mil, 7 x DIP-16, 300 mil, 4 x DIP-20, 300 mil, 1 x DIP-28, 300 mil, 1 x DIP-28, 600 mil, 1 x DIP-40, 600 mil, 1 x DIP-48, 600 mil

**Jumper shunts:** 4 x 2.54 mm, one each for JP1, JP2, JP3, SV1.

Totals: 24 ICs, 83 parts.

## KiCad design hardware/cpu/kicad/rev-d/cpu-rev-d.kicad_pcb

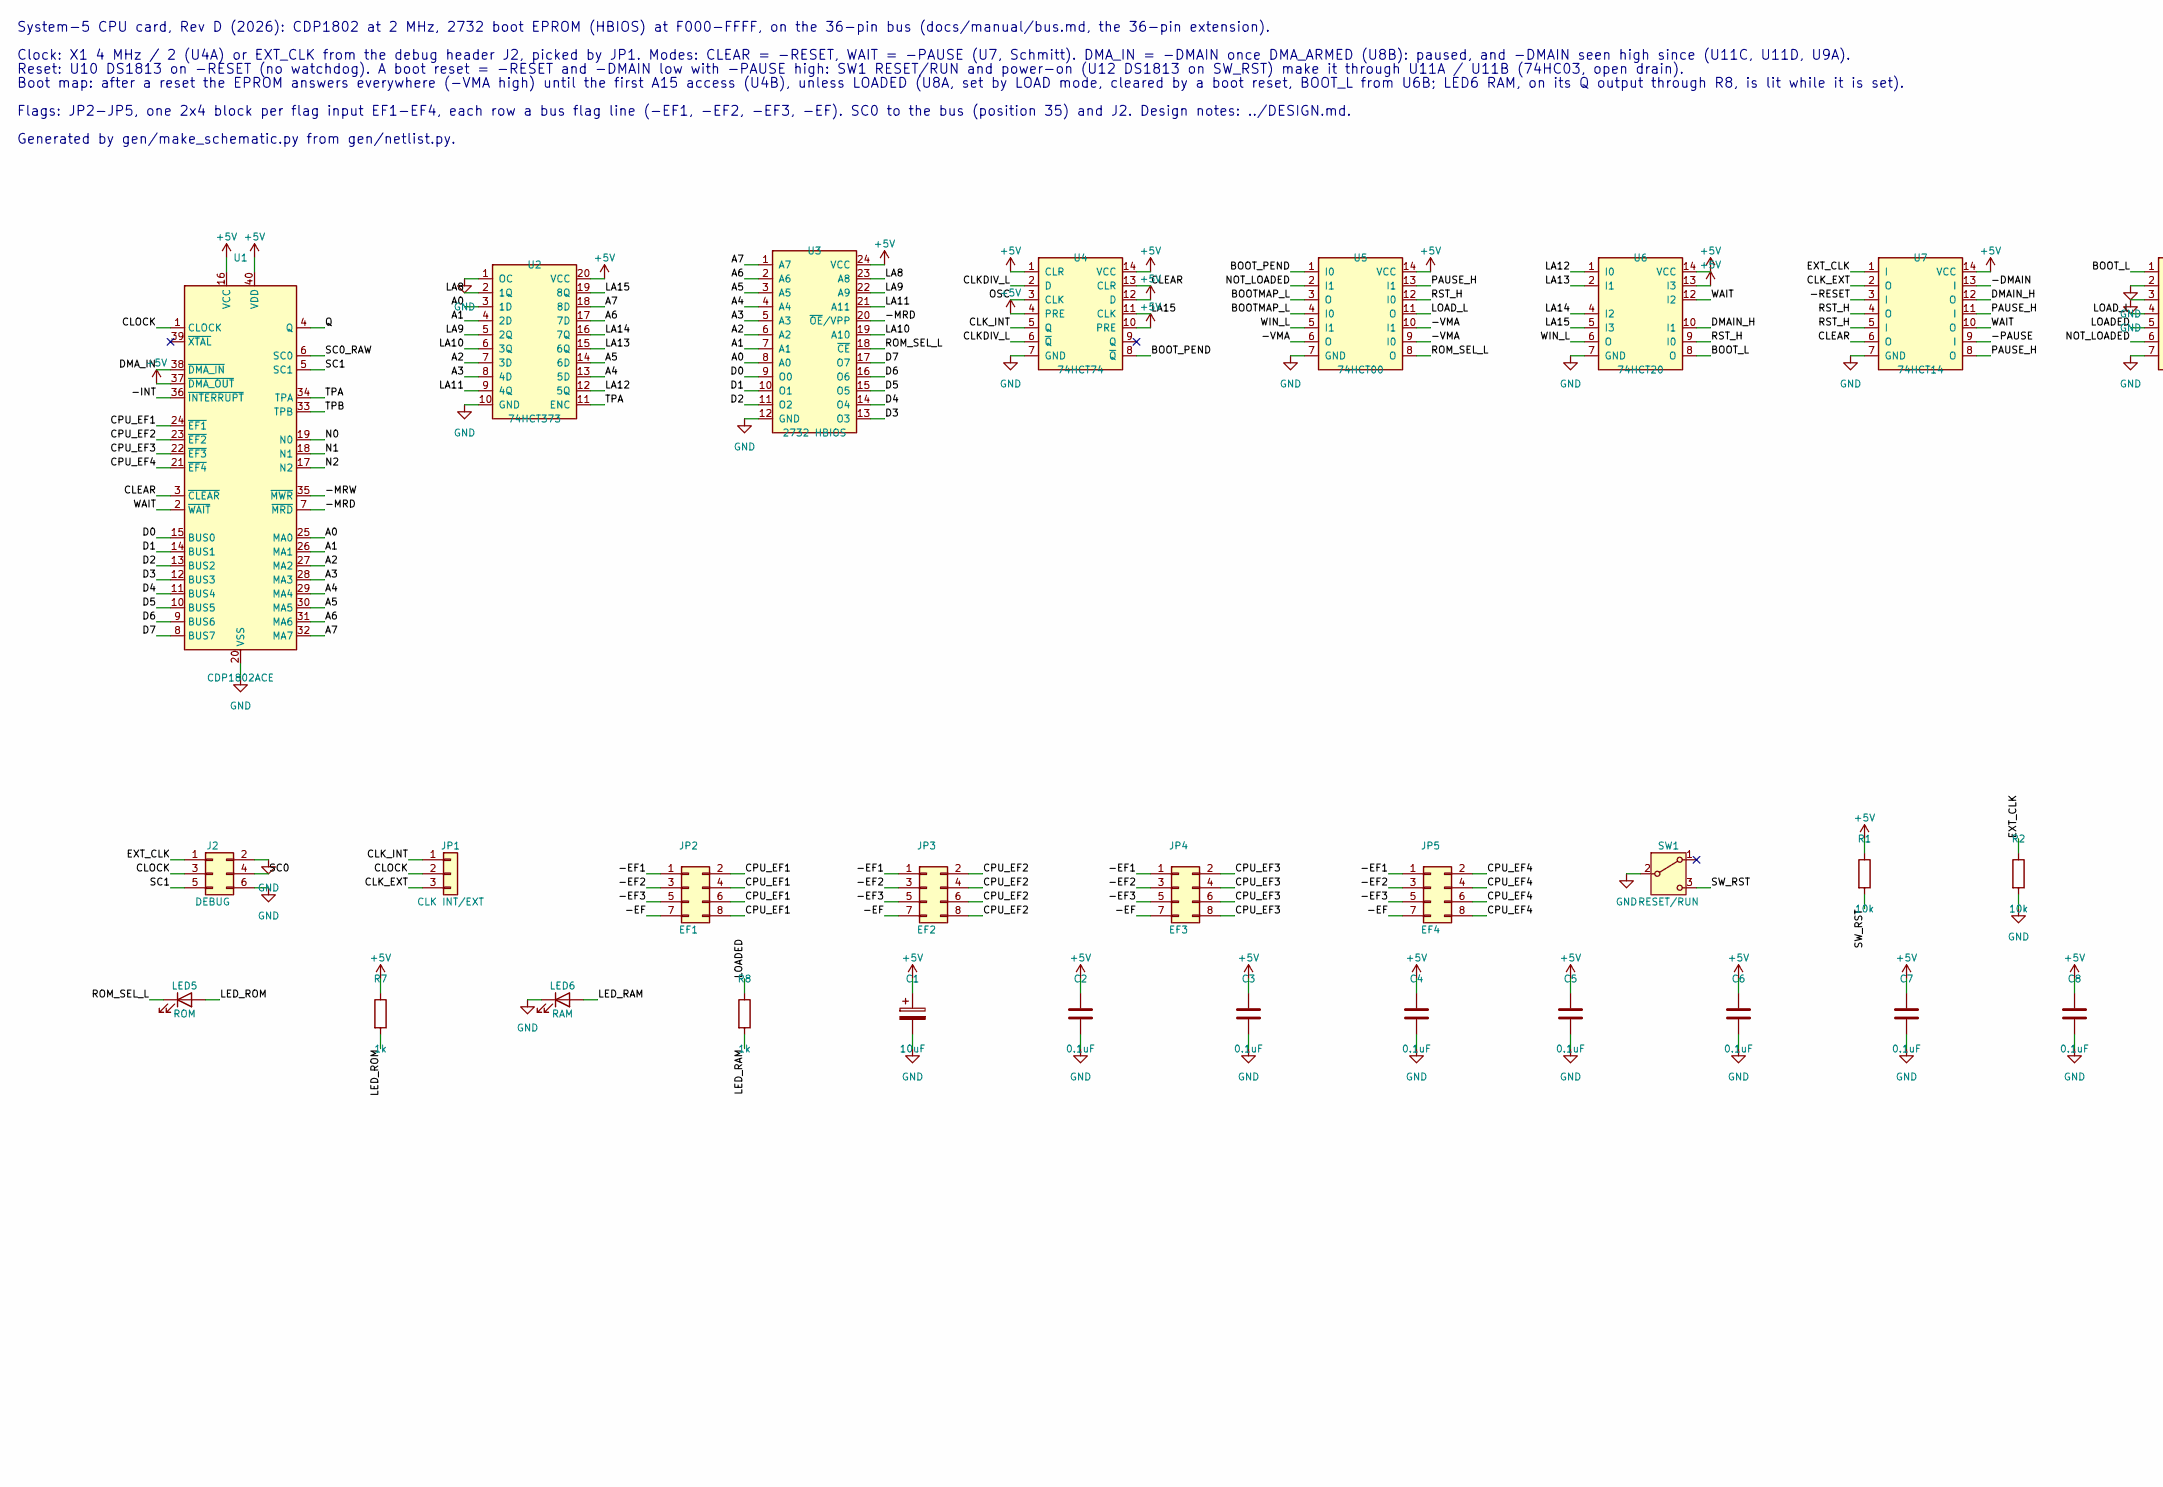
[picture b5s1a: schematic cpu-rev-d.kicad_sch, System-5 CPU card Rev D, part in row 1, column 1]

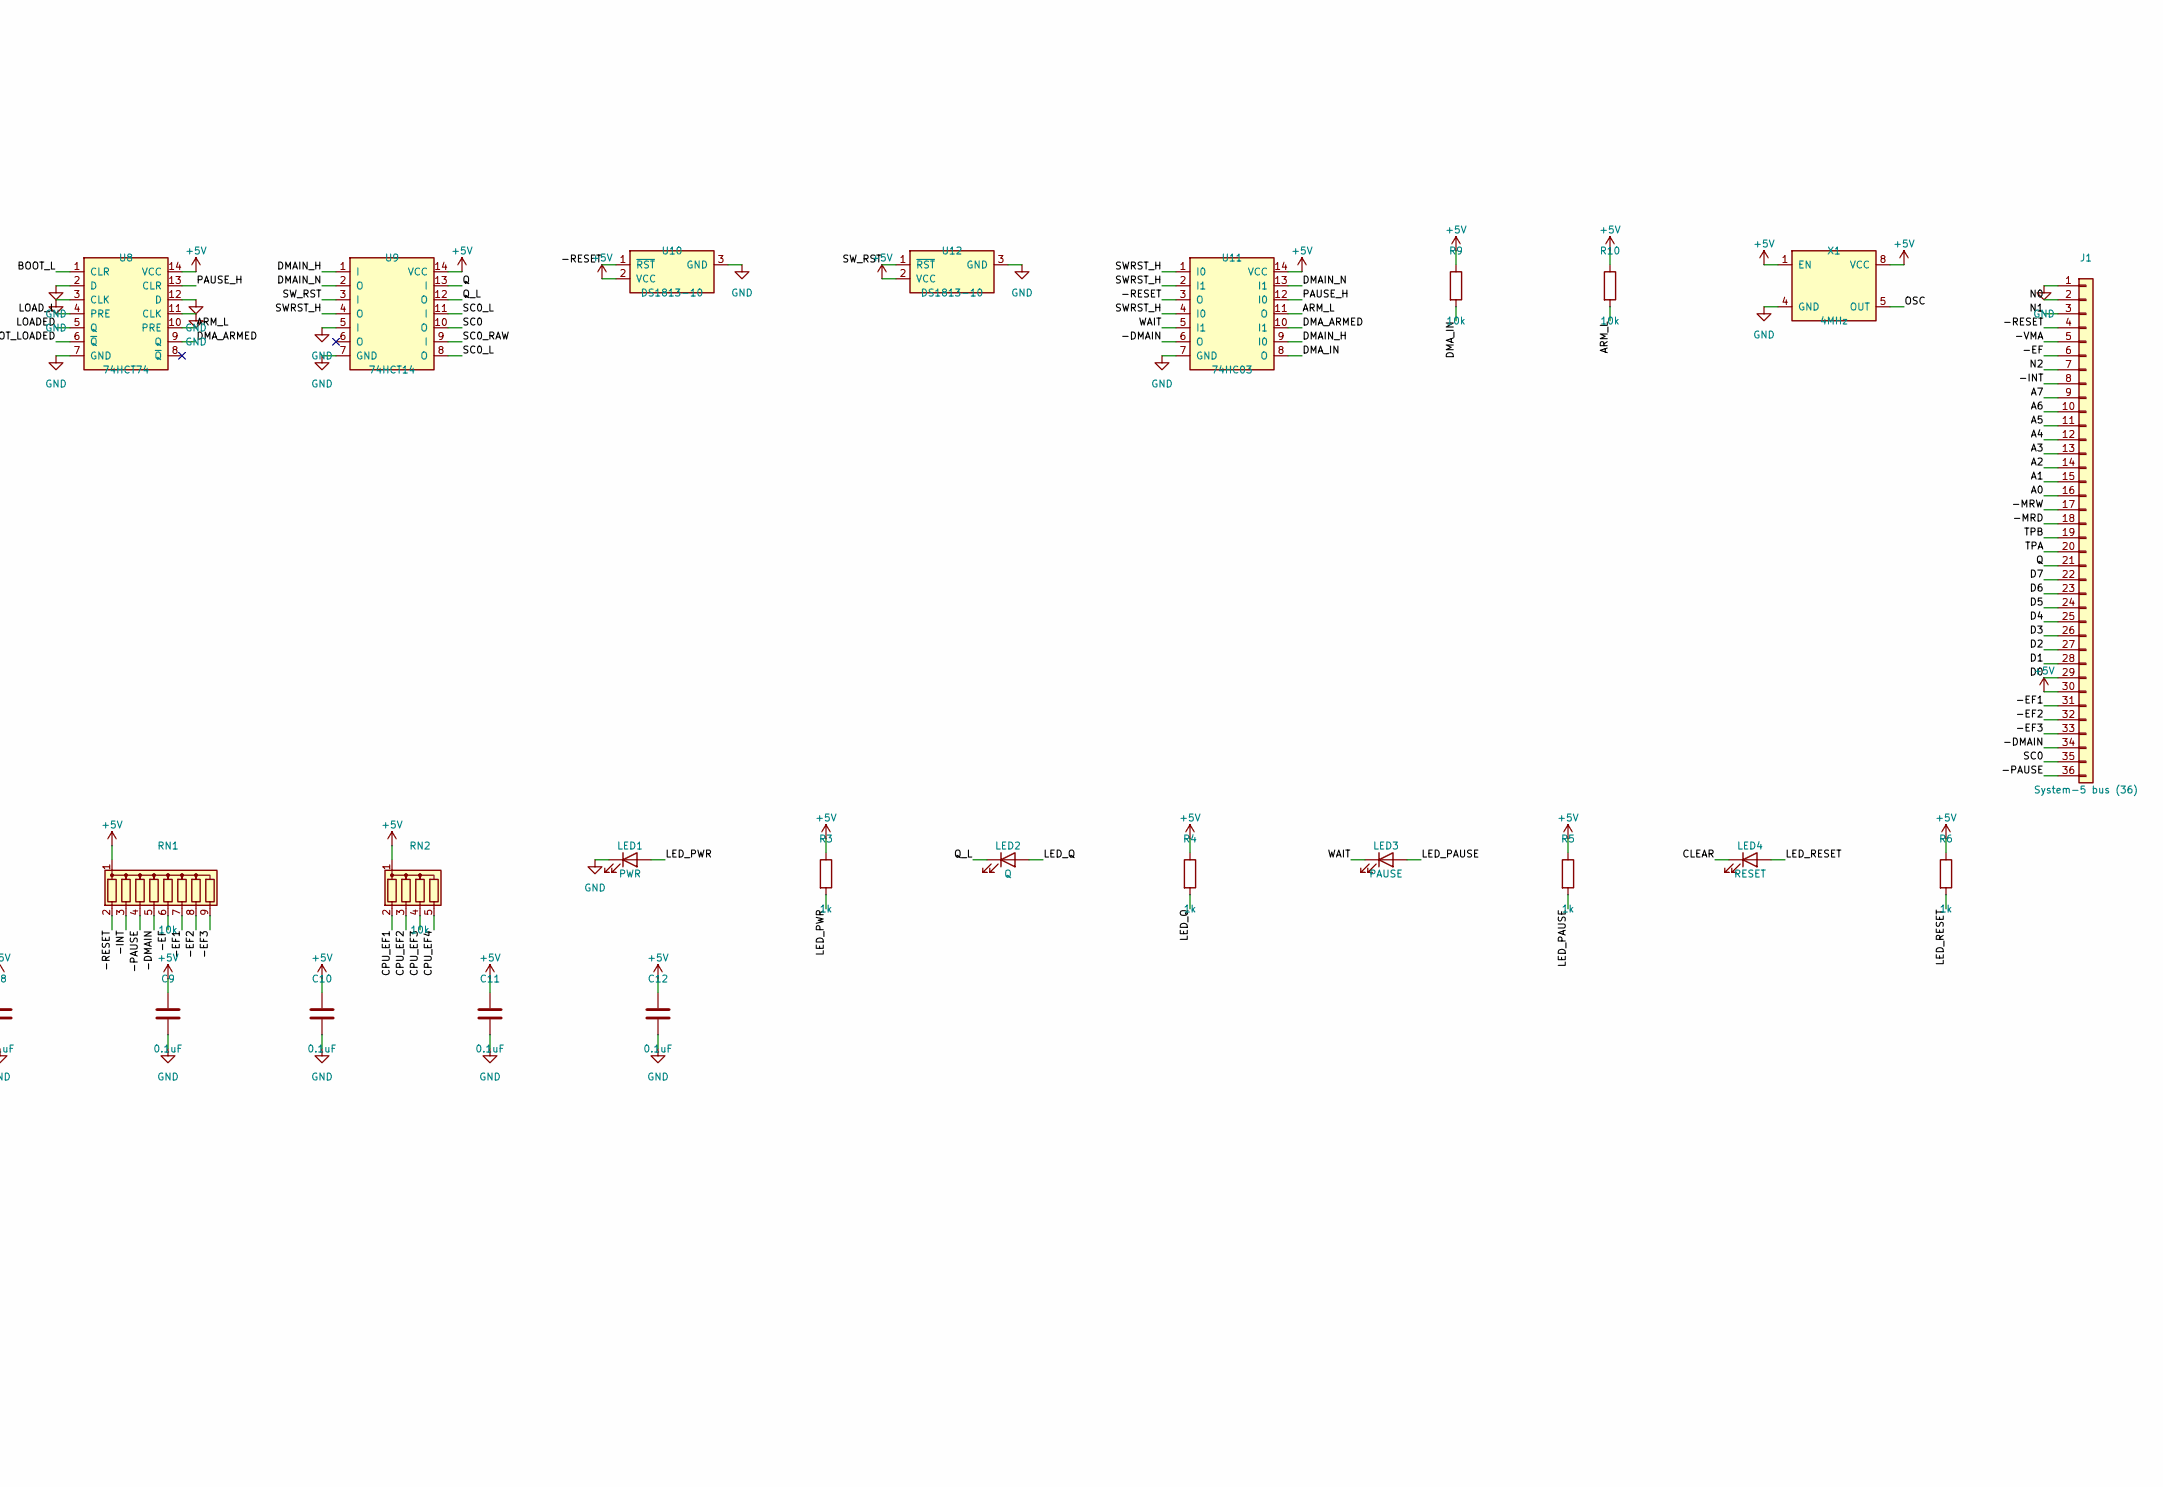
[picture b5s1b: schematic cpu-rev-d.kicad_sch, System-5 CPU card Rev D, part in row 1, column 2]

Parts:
C1: 10uF; CP_Radial_D5.0mm_P2.00mm
C2, C3, C4, C5, C6, C7, C8, C9, C10, C11, C12: 0.1uF; C025-050X050
J1: System-5 bus (36); C36
J2: DEBUG; IDC-Header_2x03_P2.54mm_Vertical
JP1: CLK INT/EXT; PinHeader_1x03_P2.54mm_Vertical
JP2: EF1; PinHeader_2x04_P2.54mm_Vertical
JP3: EF2; PinHeader_2x04_P2.54mm_Vertical
JP4: EF3; PinHeader_2x04_P2.54mm_Vertical
JP5: EF4; PinHeader_2x04_P2.54mm_Vertical
LED1: PWR; LED_D3.0mm
LED2: Q; LED_D3.0mm
LED3: PAUSE; LED_D3.0mm
LED4: RESET; LED_D3.0mm
LED5: ROM; LED_D3.0mm
LED6: RAM; LED_D3.0mm
R1, R2, R9, R10: 10k; R_Axial_DIN0207_L6.3mm_D2.5mm_P7.62mm_Horizontal
R3, R4, R5, R6, R7, R8: 1k; R_Axial_DIN0207_L6.3mm_D2.5mm_P7.62mm_Horizontal
RN1: 10k; R_Array_SIP9
RN2: 10k; R_Array_SIP5
SW1: RESET/RUN; SW_Toggle_SPDT_Marquardt_9070-1W
U1: CDP1802ACE; DIP-40_W15.24mm
U2: 74HCT373; DIP-20_W7.62mm
U3: 2732 HBIOS; DIP-24_W15.24mm
U4, U8: 74HCT74; DIP-14_W7.62mm
U5: 74HCT00; DIP-14_W7.62mm
U6: 74HCT20; DIP-14_W7.62mm
U7, U9: 74HCT14; DIP-14_W7.62mm
U10, U12: DS1813-10; TO-92_Inline
U11: 74HC03; DIP-14_W7.62mm
X1: 4MHz; Oscillator_DIP-8

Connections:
+5V: C1.1, C2.1, C3.1, C4.1, C5.1, C6.1, C7.1, C8.1, C9.1, C10.1, C11.1, C12.1, J1.30, R1.1, R3.1, R4.1, R5.1, R6.1, R7.1, R9.1, R10.1, RN1.1 (common), RN2.1 (common), U1.16 (VCC), U1.37 (~DMA_OUT), U1.40 (VDD), U2.20 (VCC), U3.24 (VCC), U4.1 (CLR), U4.4 (PRE), U4.10 (PRE), U4.12 (D), U4.14 (VCC), U5.14 (VCC), U6.13 (I3), U6.14 (VCC), U7.14 (VCC), U8.14 (VCC), U9.14 (VCC), U10.2 (VCC), U11.14 (VCC), U12.2 (VCC), X1.1 (EN), X1.8 (VCC)
/-DMAIN: J1.34, RN1.5 (R4), U7.13 (I), U11.6 (O)
/-EF: J1.6, JP2.7, JP3.7, JP4.7, JP5.7, RN1.6 (R5)
/-EF1: J1.31, JP2.1, JP3.1, JP4.1, JP5.1, RN1.7 (R6)
/-EF2: J1.32, JP2.3, JP3.3, JP4.3, JP5.3, RN1.8 (R7)
/-EF3: J1.33, JP2.5, JP3.5, JP4.5, JP5.5, RN1.9 (R8)
/-INT: J1.8, RN1.3 (R2), U1.36 (~INTERRUPT)
/-MRD: J1.18, U1.7 (~MRD), U3.20 (~OE/VPP)
/-MRW: J1.17, U1.35 (~MWR)
/-PAUSE: J1.36, RN1.4 (R3), U7.9 (I)
/-RESET: J1.4, RN1.2 (R1), U7.3 (I), U10.1 (~RST), U11.3 (O)
/-VMA: J1.5, U5.6 (O), U5.9 (I0), U5.10 (I1)
/A0: J1.16, U1.25 (MA0), U2.3 (1D), U3.8 (A0)
/A1: J1.15, U1.26 (MA1), U2.4 (2D), U3.7 (A1)
/A2: J1.14, U1.27 (MA2), U2.7 (3D), U3.6 (A2)
/A3: J1.13, U1.28 (MA3), U2.8 (4D), U3.5 (A3)
/A4: J1.12, U1.29 (MA4), U2.13 (5D), U3.4 (A4)
/A5: J1.11, U1.30 (MA5), U2.14 (6D), U3.3 (A5)
/A6: J1.10, U1.31 (MA6), U2.17 (7D), U3.2 (A6)
/A7: J1.9, U1.32 (MA7), U2.18 (8D), U3.1 (A7)
/ARM_L: R10.2, U8.10 (PRE), U11.11 (O)
/BOOTMAP_L: U5.3 (O), U5.4 (I0)
/BOOT_L: U6.8 (O), U8.1 (CLR)
/BOOT_PEND: U4.8 (~Q), U5.1 (I0)
/CLEAR: LED4.1 (K), U1.3 (~CLEAR), U4.13 (CLR), U7.6 (O)
/CLKDIV_L: U4.2 (D), U4.6 (~Q)
/CLK_EXT: JP1.3, U7.2 (O)
/CLK_INT: JP1.1, U4.5 (Q)
/CLOCK: J2.3, JP1.2, U1.1 (CLOCK)
/CPU_EF1: JP2.2, JP2.4, JP2.6, JP2.8, RN2.2 (R1), U1.24 (~EF1)
/CPU_EF2: JP3.2, JP3.4, JP3.6, JP3.8, RN2.3 (R2), U1.23 (~EF2)
/CPU_EF3: JP4.2, JP4.4, JP4.6, JP4.8, RN2.4 (R3), U1.22 (~EF3)
/CPU_EF4: JP5.2, JP5.4, JP5.6, JP5.8, RN2.5 (R4), U1.21 (~EF4)
/D0: J1.29, U1.15 (BUS0), U3.9 (O0)
/D1: J1.28, U1.14 (BUS1), U3.10 (O1)
/D2: J1.27, U1.13 (BUS2), U3.11 (O2)
/D3: J1.26, U1.12 (BUS3), U3.13 (O3)
/D4: J1.25, U1.11 (BUS4), U3.14 (O4)
/D5: J1.24, U1.10 (BUS5), U3.15 (O5)
/D6: J1.23, U1.9 (BUS6), U3.16 (O6)
/D7: J1.22, U1.8 (BUS7), U3.17 (O7)
/DMAIN_H: U6.10 (I1), U7.12 (O), U9.1 (I), U11.9 (I0)
/DMAIN_N: U9.2 (O), U11.13 (I1)
/DMA_ARMED: U8.9 (Q), U11.10 (I1)
/DMA_IN: R9.2, U1.38 (~DMA_IN), U11.8 (O)
/EXT_CLK: J2.1, R2.1, U7.1 (I)
/LA8: U2.2 (1Q), U3.23 (A8)
/LA9: U2.5 (2Q), U3.22 (A9)
/LA10: U2.6 (3Q), U3.19 (A10)
/LA11: U2.9 (4Q), U3.21 (A11)
/LA12: U2.12 (5Q), U6.1 (I0)
/LA13: U2.15 (6Q), U6.2 (I1)
/LA14: U2.16 (7Q), U6.4 (I2)
/LA15: U2.19 (8Q), U4.11 (CLK), U6.5 (I3)
/LED_PAUSE: LED3.2 (A), R5.2
/LED_PWR: LED1.2 (A), R3.2
/LED_Q: LED2.2 (A), R4.2
/LED_RAM: LED6.2 (A), R8.2
/LED_RESET: LED4.2 (A), R6.2
/LED_ROM: LED5.2 (A), R7.2
/LOADED: R8.1, U8.5 (Q)
/LOAD_L: U5.11 (O), U8.4 (PRE)
/N0: J1.2, U1.19 (N0)
/N1: J1.3, U1.18 (N1)
/N2: J1.7, U1.17 (N2)
/NOT_LOADED: U5.2 (I1), U8.6 (~Q)
/OSC: U4.3 (CLK), X1.5 (OUT)
/PAUSE_H: U5.13 (I1), U7.8 (O), U7.11 (I), U8.13 (CLR), U11.12 (I0)
/Q: J1.21, U1.4 (Q), U9.13 (I)
/Q_L: LED2.1 (K), U9.12 (O)
/ROM_SEL_L: LED5.1 (K), U3.18 (~CE), U5.8 (O)
/RST_H: U5.12 (I0), U6.9 (I0), U7.4 (O), U7.5 (I)
/SC0: J1.35, J2.4, U9.10 (O)
/SC0_L: U9.8 (O), U9.11 (I)
/SC0_RAW: U1.6 (SC0), U9.9 (I)
/SC1: J2.5, U1.5 (SC1)
/SWRST_H: U9.4 (O), U11.1 (I0), U11.2 (I1), U11.4 (I0)
/SW_RST: R1.2, SW1.3 (C), U9.3 (I), U12.1 (~RST)
/TPA: J1.20, U1.34 (TPA), U2.11 (ENC)
/TPB: J1.19, U1.33 (TPB)
/WAIT: LED3.1 (K), U1.2 (~WAIT), U6.12 (I2), U7.10 (O), U11.5 (I1)
/WIN_L: U5.5 (I1), U6.6 (O)
GND: C1.2, C2.2, C3.2, C4.2, C5.2, C6.2, C7.2, C8.2, C9.2, C10.2, C11.2, C12.2, J1.1, J2.2, J2.6, LED1.1 (K), LED6.1 (K), R2.2, SW1.2 (B), U1.20 (VSS), U2.1 (OC), U2.10 (GND), U3.12 (GND), U4.7 (GND), U5.7 (GND), U6.7 (GND), U7.7 (GND), U8.2 (D), U8.3 (CLK), U8.7 (GND), U8.11 (CLK), U8.12 (D), U9.5 (I), U9.7 (GND), U10.3 (GND), U11.7 (GND), U12.3 (GND), X1.4 (GND)

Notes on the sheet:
System-5 CPU card, Rev D (2026): CDP1802 at 2 MHz, 2732 boot EPROM (HBIOS) at F000-FFFF, on the 36-pin bus (docs/manual/bus.md, the 36-pin extension).
Clock: X1 4 MHz / 2 (U4A) or EXT_CLK from the debug header J2, picked by JP1. Modes: CLEAR = -RESET, WAIT = -PAUSE (U7, Schmitt). DMA_IN = -DMAIN once DMA_ARMED (U8B): paused, and -DMAIN seen high since (U11C, U11D, U9A).
Reset: U10 DS1813 on -RESET (no watchdog). A boot reset = -RESET and -DMAIN low with -PAUSE high: SW1 RESET/RUN and power-on (U12 DS1813 on SW_RST) make it through U11A / U11B (74HC03, open drain).
Boot map: after a reset the EPROM answers everywhere (-VMA high) until the first A15 access (U4B), unless LOADED (U8A, set by LOAD mode, cleared by a boot reset, BOOT_L from U6B; LED6 RAM, on its Q output through R8, is lit while it is set).
Flags: JP2-JP5, one 2x4 block per flag input EF1-EF4, each row a bus flag line (-EF1, -EF2, -EF3, -EF). SC0 to the bus (position 35) and J2. Design notes: ../DESIGN.md.
Generated by gen/make_schematic.py from gen/netlist.py.
